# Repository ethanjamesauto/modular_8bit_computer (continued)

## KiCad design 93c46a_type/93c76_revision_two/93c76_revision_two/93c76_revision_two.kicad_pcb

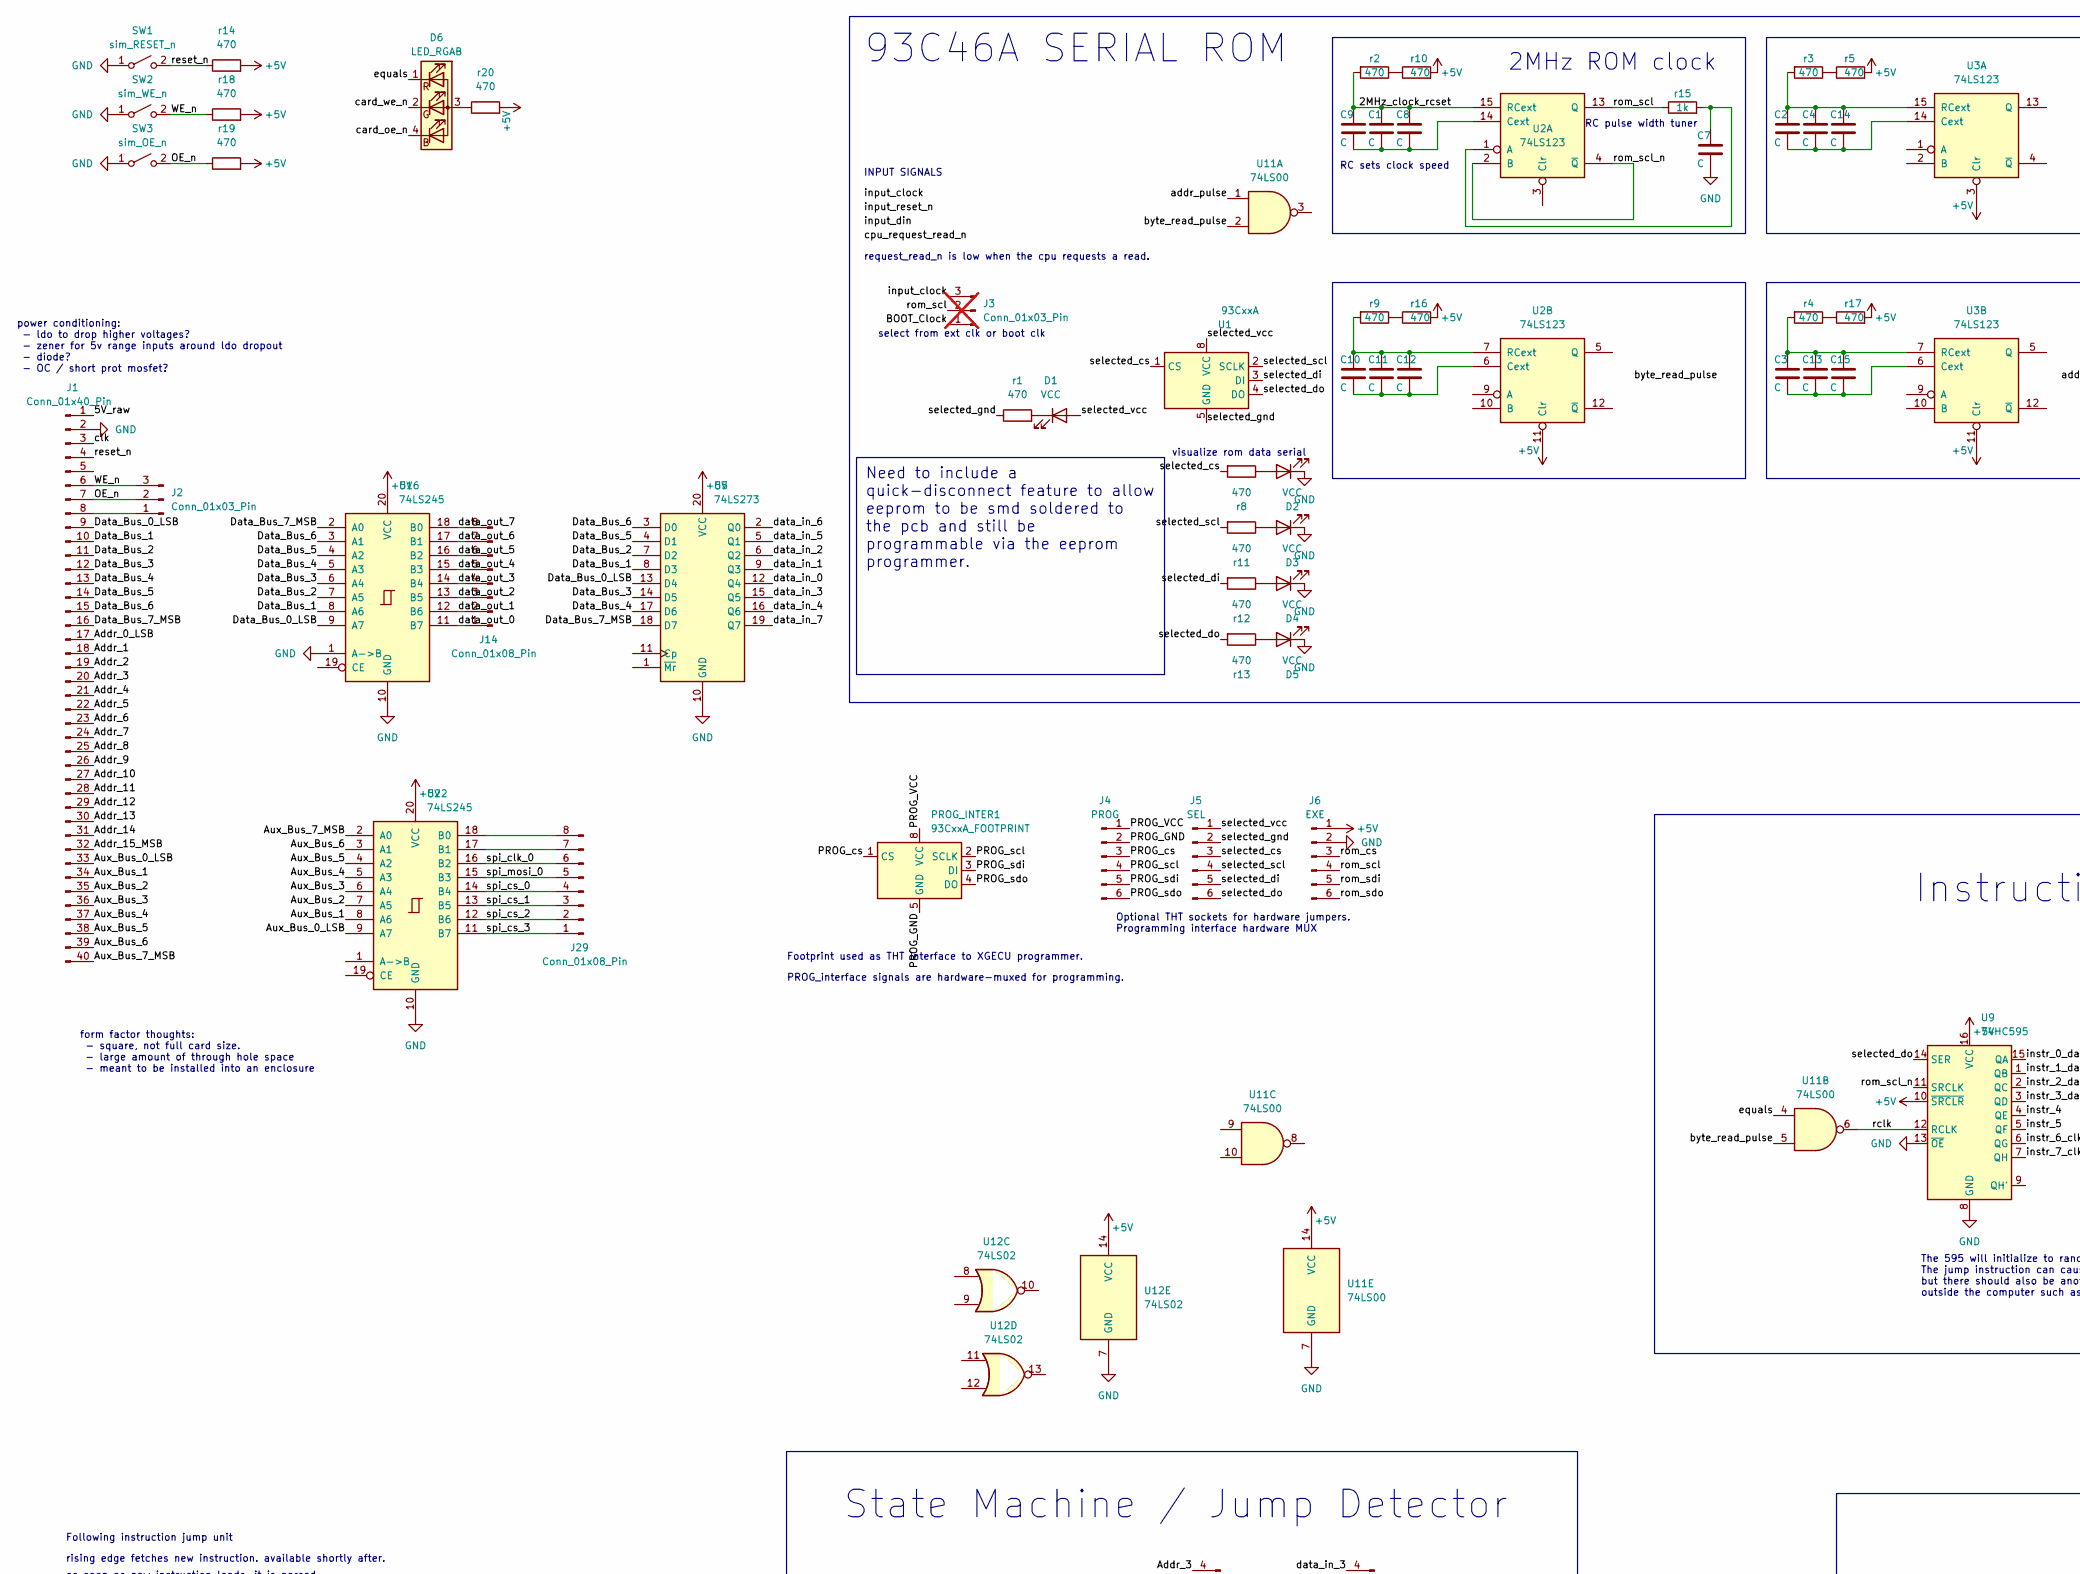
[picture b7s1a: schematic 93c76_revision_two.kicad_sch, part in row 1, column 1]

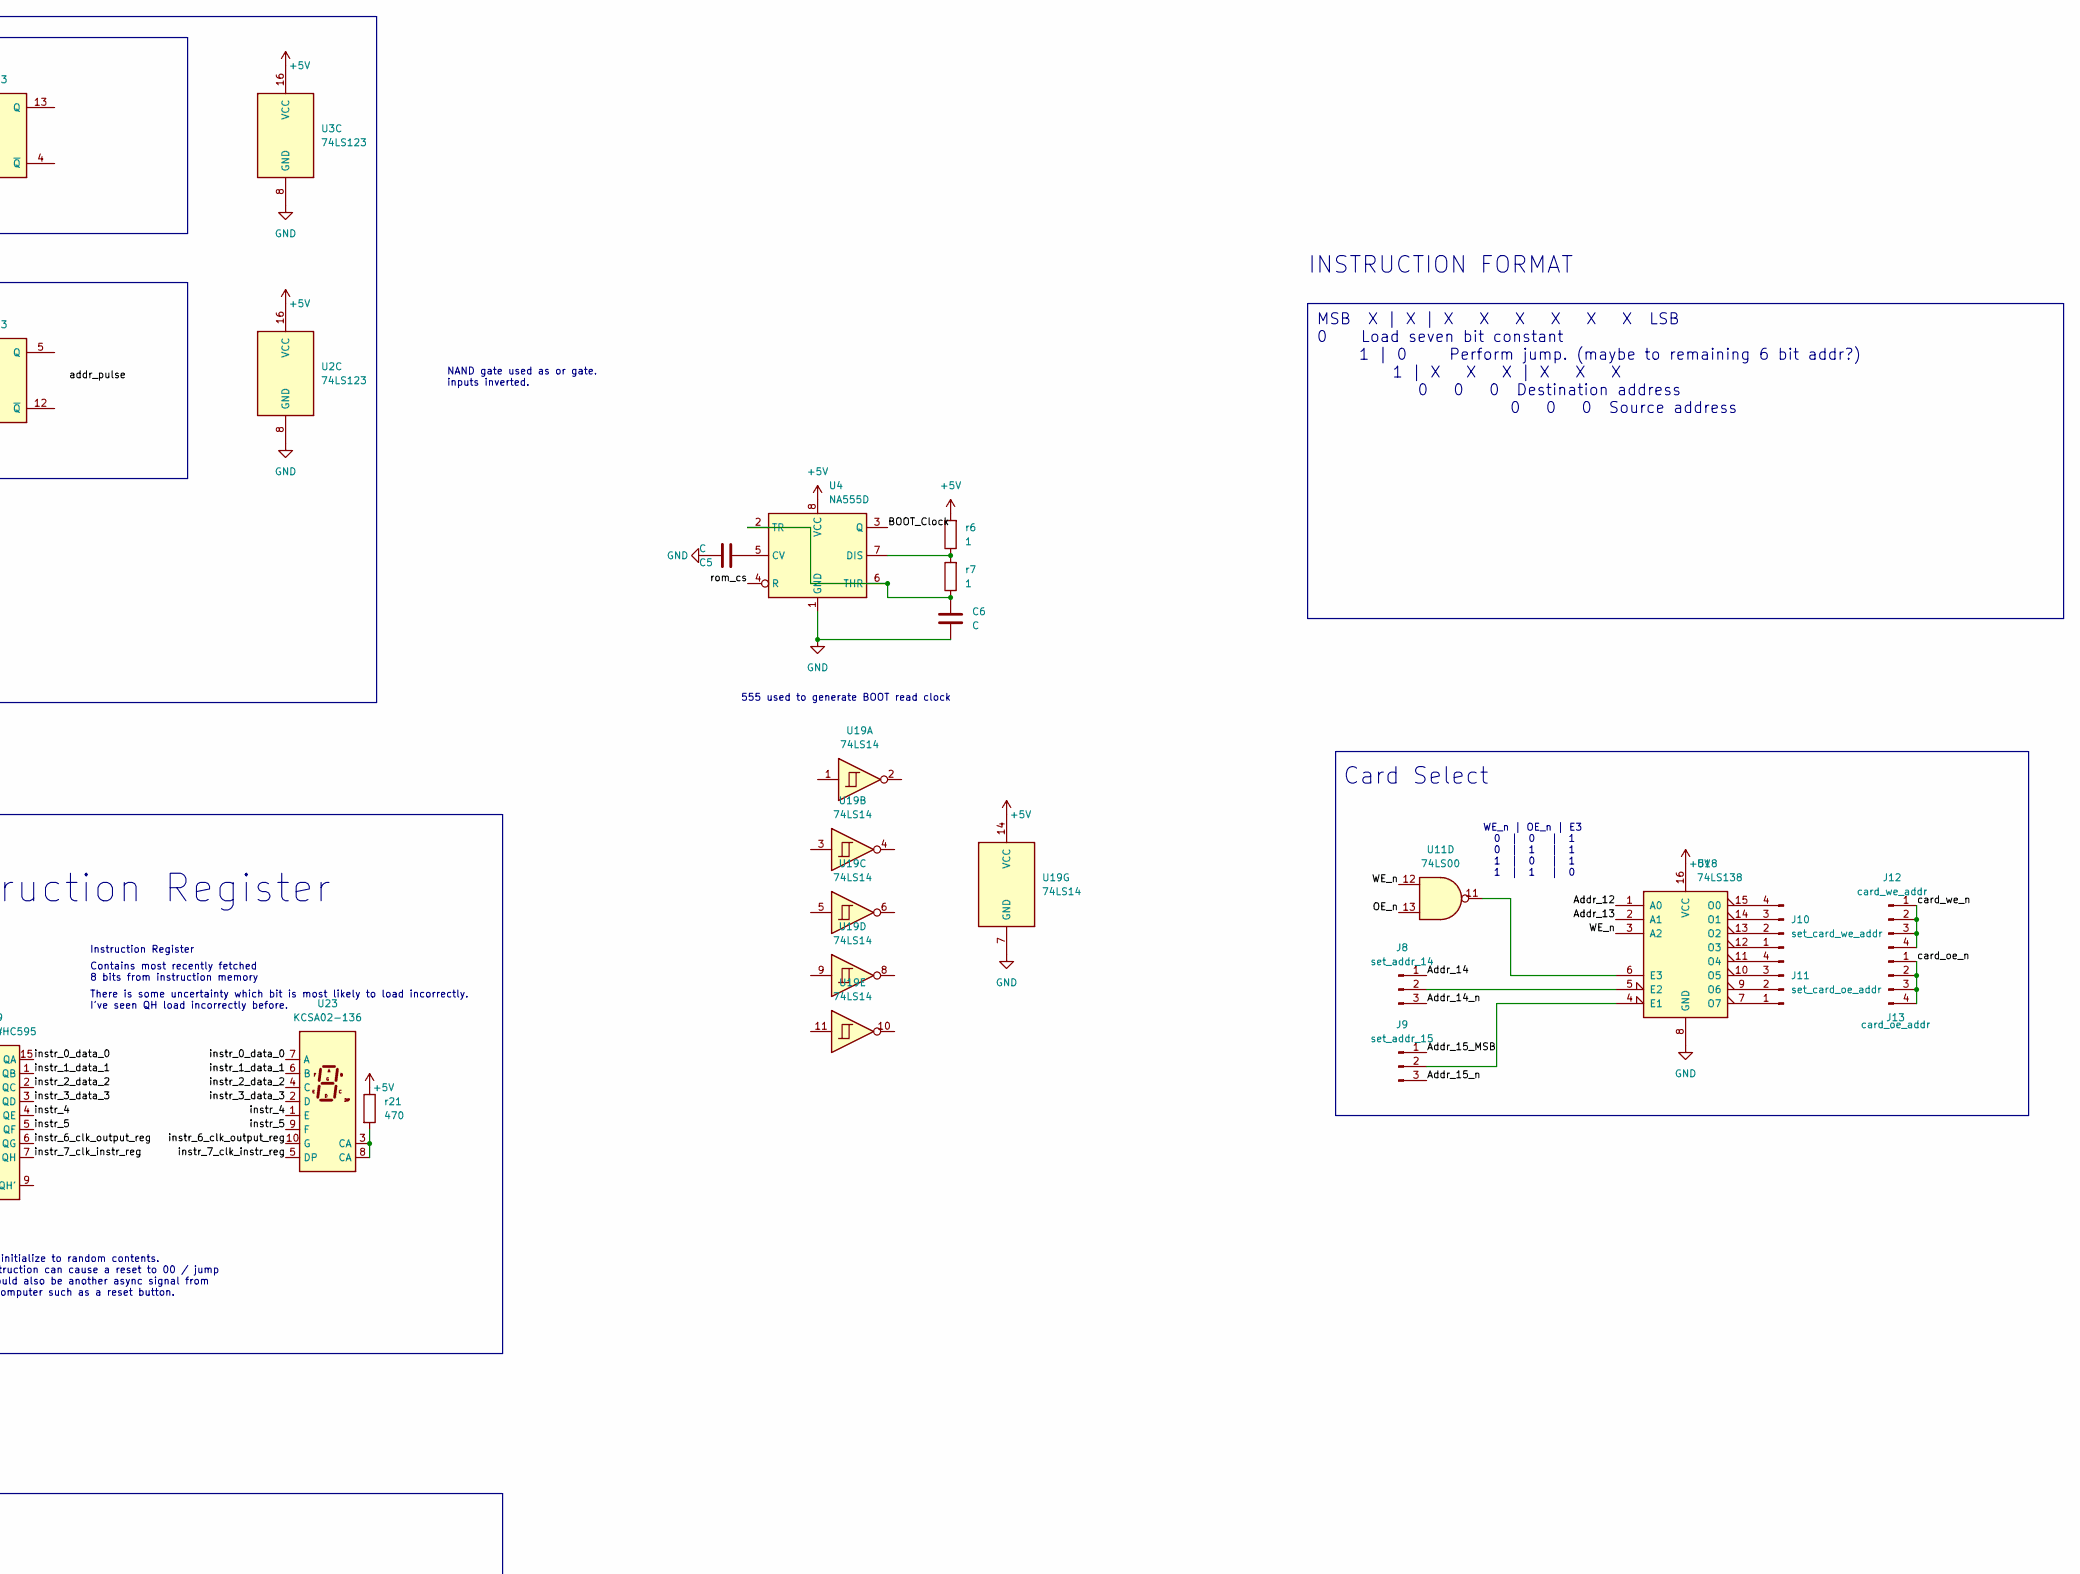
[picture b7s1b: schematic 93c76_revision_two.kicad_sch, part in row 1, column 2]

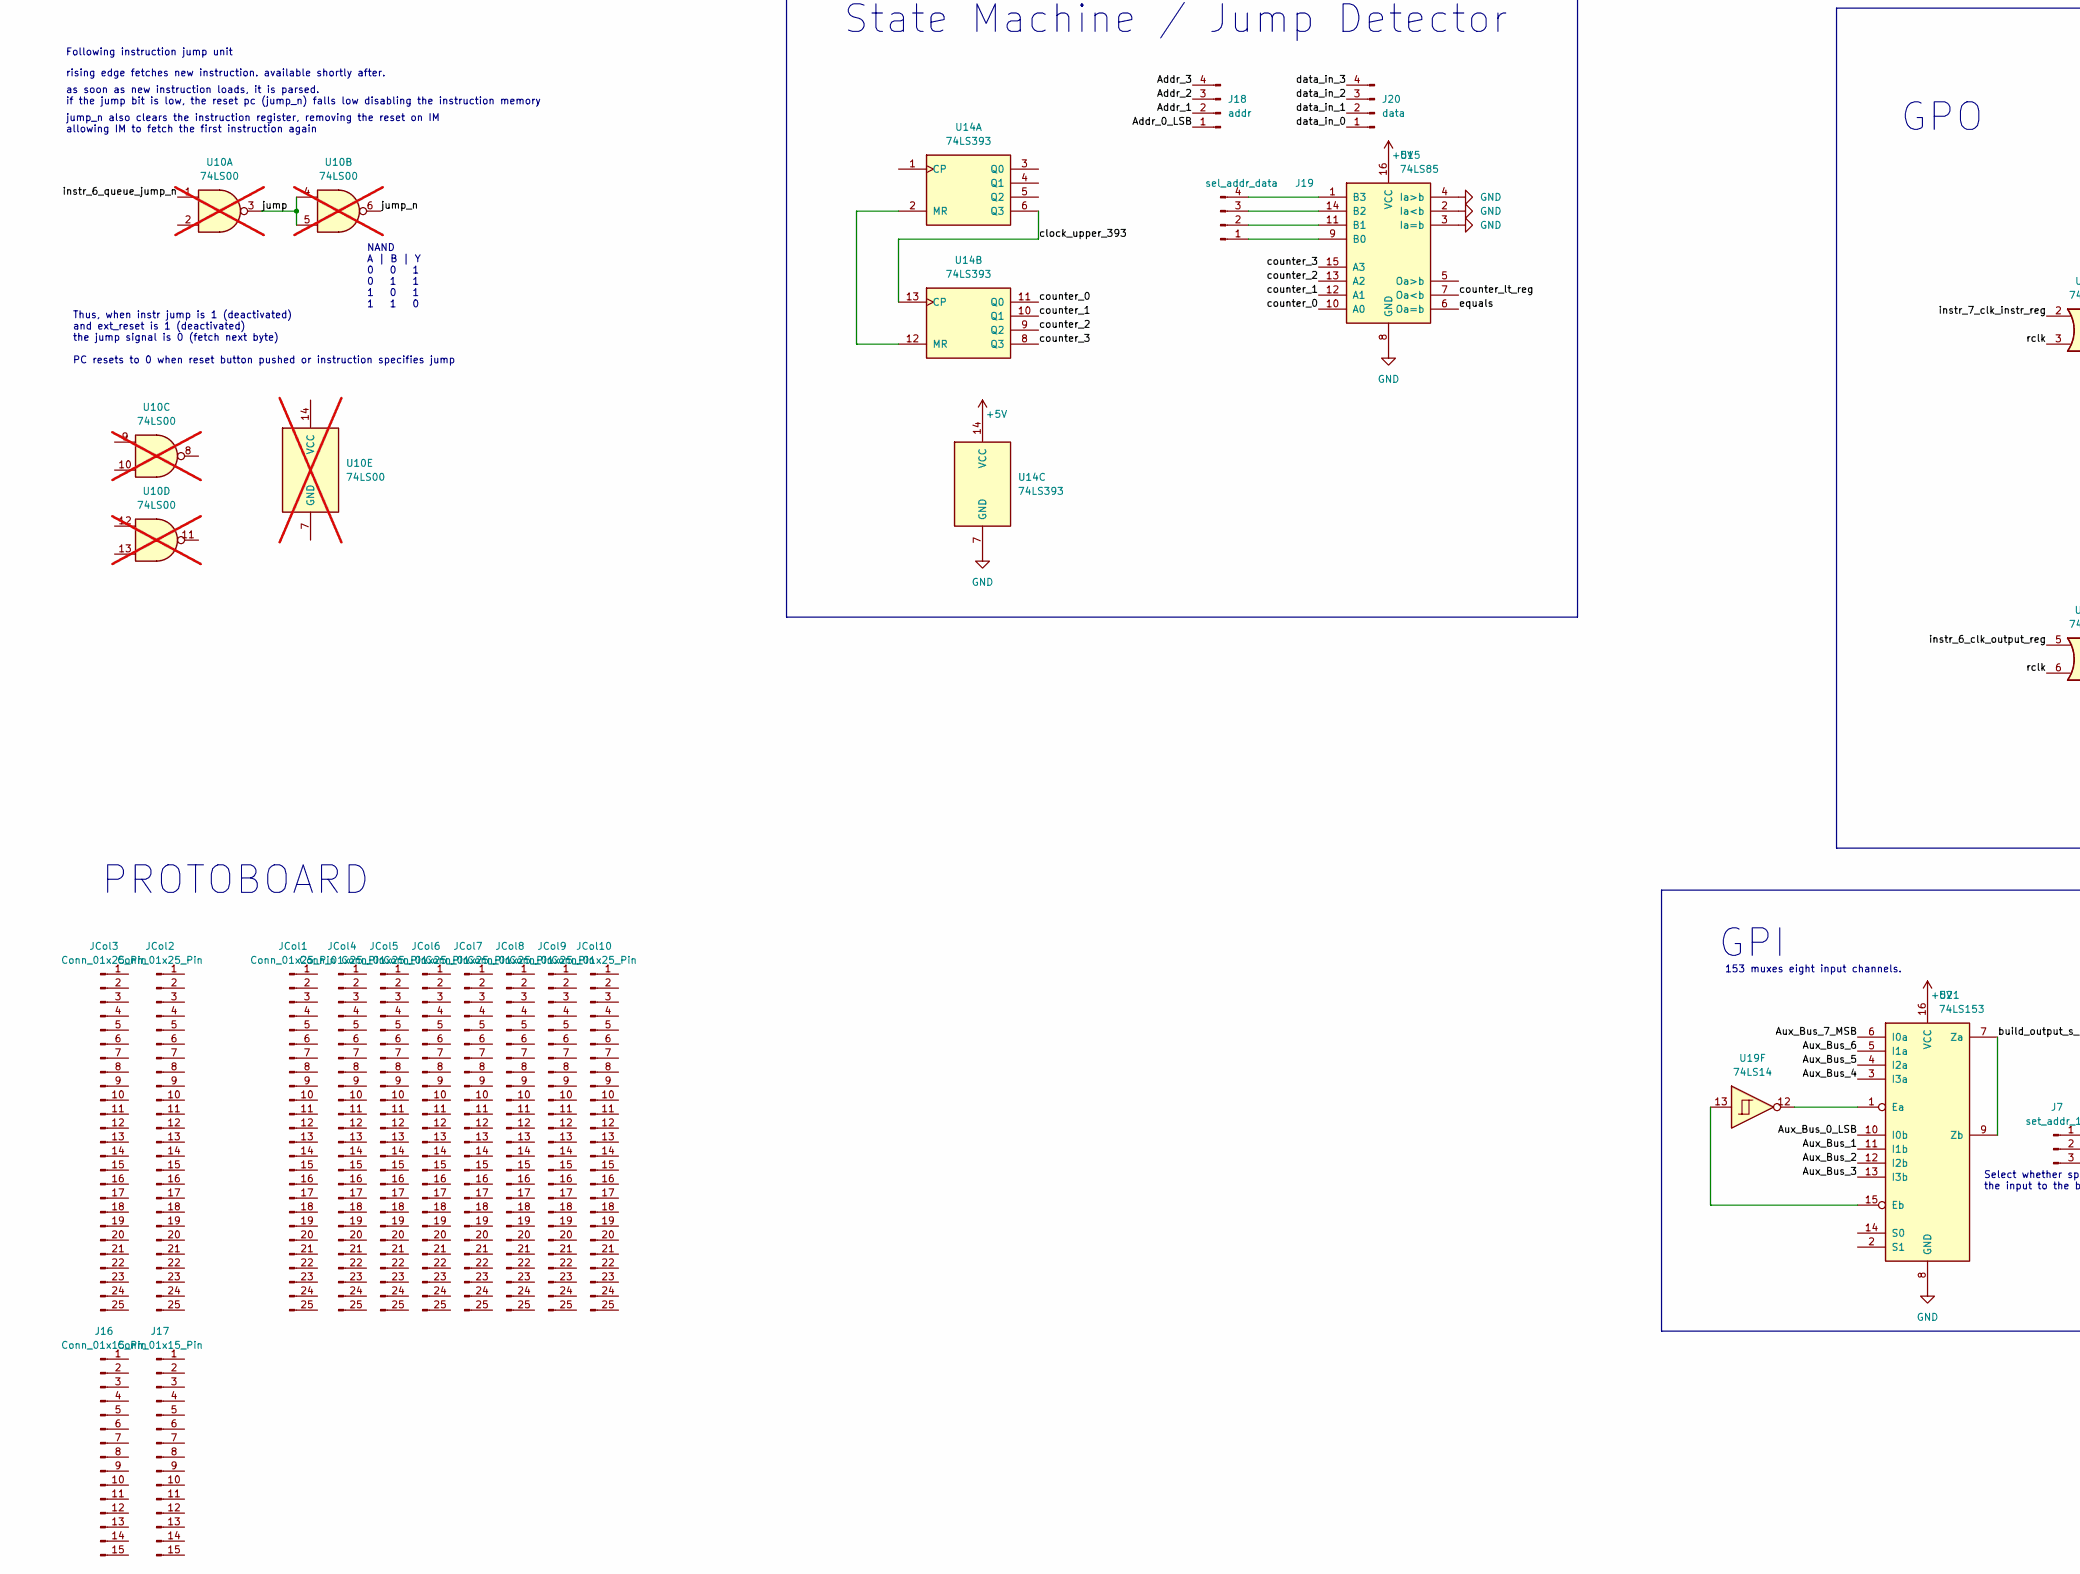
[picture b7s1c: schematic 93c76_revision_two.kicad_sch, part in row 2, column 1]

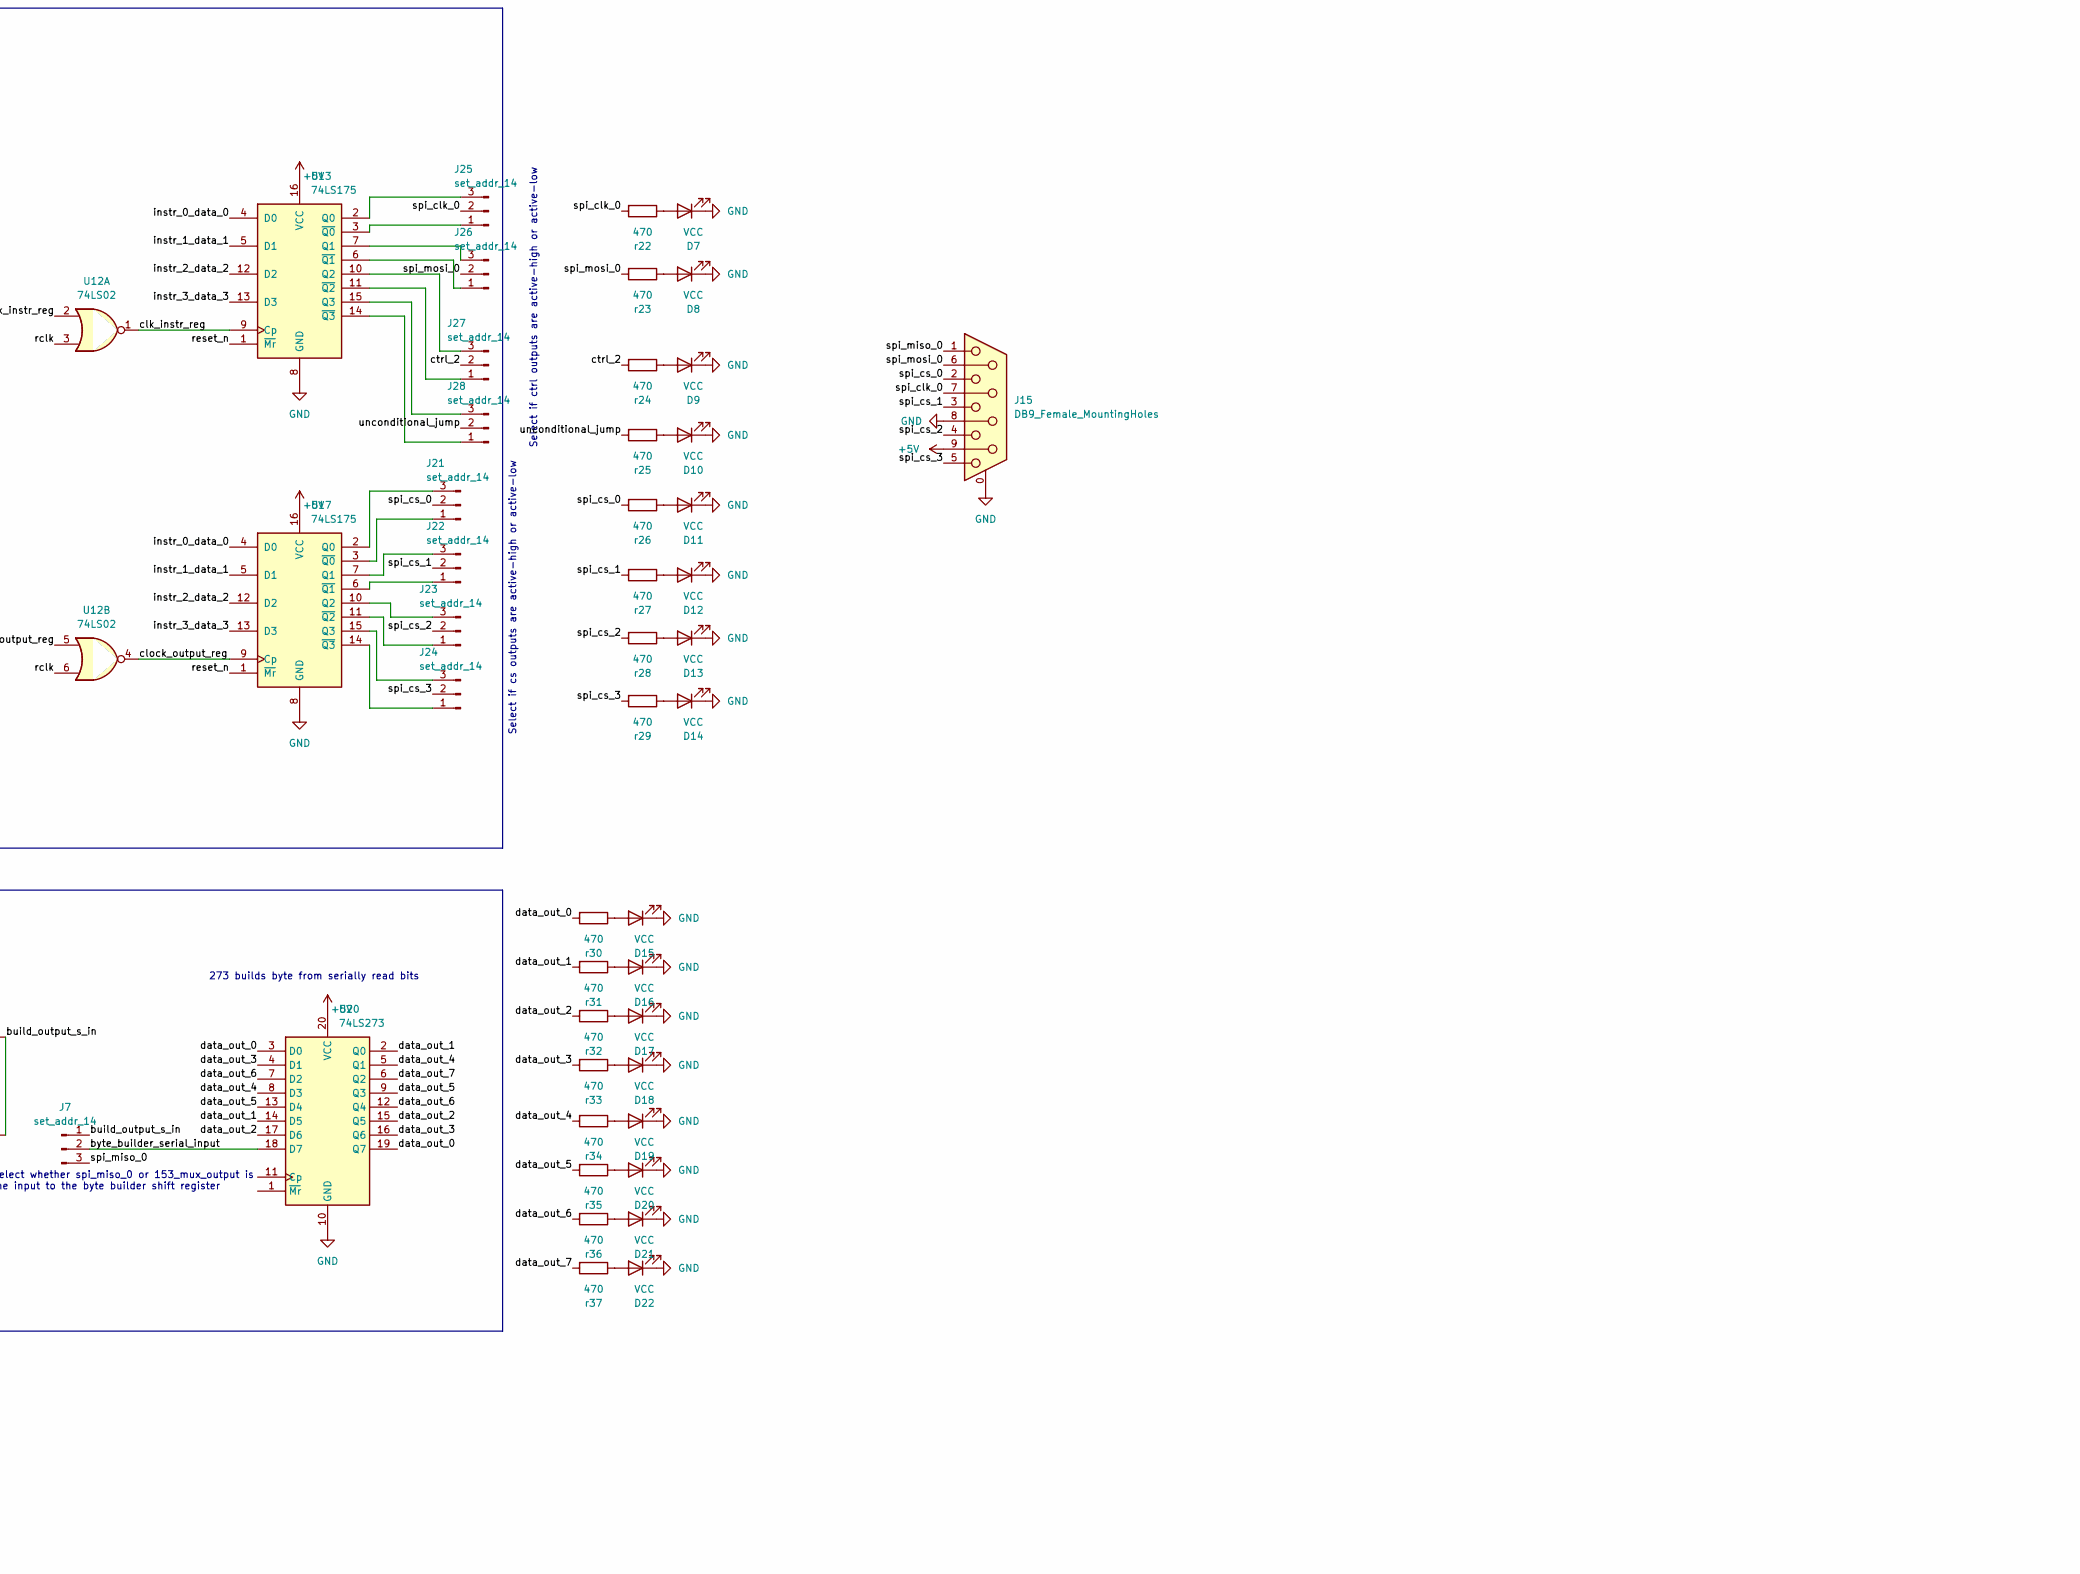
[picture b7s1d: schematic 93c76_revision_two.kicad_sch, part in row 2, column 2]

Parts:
C1, C2, C3, C4, C5, C6, C7, C8, C9, C10, C11, C12, C13, C14, C15: C; C_Disc_D3.0mm_W2.0mm_P2.50mm
D1, D2, D3, D4, D5, D7, D8, D9, D10, D11, D12, D13, D14, D15, D16, D17, D18, D19, D20, D21, D22: VCC; LED_0603_1608Metric_Pad1.05x0.95mm_HandSolder
D6: LED_RGAB; LED_D5.0mm-4_RGB
J1: Conn_01x40_Pin; PinHeader_1x40_P2.54mm_Horizontal
J2: Conn_01x03_Pin; PinHeader_1x03_P2.54mm_Vertical
J3: Conn_01x03_Pin; PinHeader_1x03_P2.54mm_Vertical; not fitted
J4: PROG; PinHeader_1x06_P2.54mm_Vertical
J5: SEL; PinHeader_1x06_P2.54mm_Vertical
J6: EXE; PinHeader_1x06_P2.54mm_Vertical
J7, J8, J21, J22, J23, J24, J25, J26, J27, J28: set_addr_14; PinHeader_1x03_P2.54mm_Vertical
J9: set_addr_15; PinHeader_1x03_P2.54mm_Vertical
J10: set_card_we_addr; PinHeader_1x04_P2.54mm_Vertical
J11: set_card_oe_addr; PinHeader_1x04_P2.54mm_Vertical
J12: card_we_addr; PinHeader_1x04_P2.54mm_Vertical
J13: card_oe_addr; PinHeader_1x04_P2.54mm_Vertical
J14, J29: Conn_01x08_Pin; PinHeader_1x08_P2.54mm_Vertical
J15: DB9_Female_MountingHoles; DSUB-9_Female_Horizontal_P2.77x2.84mm_EdgePinOffset4.94mm_H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
J16, J17: Conn_01x15_Pin; PinHeader_1x15_P2.54mm_Vertical
J18: addr; PinHeader_1x04_P2.54mm_Vertical
J19: sel_addr_data; PinHeader_1x04_P2.54mm_Vertical
J20: data; PinHeader_1x04_P2.54mm_Vertical
JCol1, JCol2, JCol3, JCol4, JCol5, JCol6, JCol7, JCol8, JCol9, JCol10: Conn_01x25_Pin; PinHeader_1x25_P2.54mm_Vertical
PROG_INTER1: 93CxxA_FOOTPRINT; DIP-8_W7.62mm
SW1: sim_RESET_n; R_Axial_DIN0204_L3.6mm_D1.6mm_P5.08mm_Horizontal
SW2: sim_WE_n; R_Axial_DIN0204_L3.6mm_D1.6mm_P5.08mm_Horizontal
SW3: sim_OE_n; R_Axial_DIN0204_L3.6mm_D1.6mm_P5.08mm_Horizontal
U1: 93CxxA; SOIC-8_3.9x4.9mm_P1.27mm
U2, U3: 74LS123; DIP-16_W7.62mm
U4: NA555D; DIP-8_W7.62mm
U5, U20: 74LS273; DIP-20_W7.62mm
U9: 74HC595; SOIC-16_3.9x9.9mm_P1.27mm
U10: 74LS00; not fitted
U11: 74LS00; DIP-14_W7.62mm
U12: 74LS02; DIP-14_W7.62mm
U13, U17: 74LS175; DIP-16_W7.62mm
U14: 74LS393; DIP-14_W7.62mm
U15: 74LS85; DIP-16_W7.62mm
U16, U22: 74LS245; DIP-20_W7.62mm
U18: 74LS138; DIP-16_W7.62mm
U19: 74LS14; DIP-14_W7.62mm
U21: 74LS153; DIP-16_W7.62mm
U23: KCSA02-136; 7SegmentLED_LTS6760_LTS6780
r1, r8, r11, r12, r13, r14, r18, r19, r20, r21, r22, r23, r24, r25, r26, r27, r28, r29, r30, r31, r32, r33, r34, r35, r36, r37: 470; R_0603_1608Metric_Pad0.98x0.95mm_HandSolder
r2, r3, r4, r5, r9, r10, r16, r17: 470; R_Axial_DIN0204_L3.6mm_D1.6mm_P7.62mm_Horizontal
r6, r7: 1; R_Axial_DIN0204_L3.6mm_D1.6mm_P7.62mm_Horizontal
r15: 1k; R_Axial_DIN0204_L3.6mm_D1.6mm_P7.62mm_Horizontal

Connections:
+5V: J6.1, J15.9, U2.11 (Clr), U2.16 (VCC), U3.3 (Clr), U3.11 (Clr), U3.16 (VCC), U4.8 (VCC), U5.20 (VCC), U9.10 (~SRCLR), U9.16 (VCC), U11.14 (VCC), U12.14 (VCC), U13.16 (VCC), U14.14 (VCC), U15.16 (VCC), U16.20 (VCC), U17.16 (VCC), U18.16 (VCC), U19.14 (VCC), U20.20 (VCC), U21.16 (VCC), U22.20 (VCC), r5.2, r6.2, r10.2, r14.2, r16.2, r17.2, r18.2, r19.2, r20.2, r21.1
/2MHz_clock_rcset: C1.2, C8.2, C9.2, U2.15 (RCext), r2.2
/5V_raw: J1.1
/Addr_0_LSB: J1.17, J18.1
/Addr_1: J1.18, J18.2
/Addr_2: J1.19, J18.3
/Addr_3: J1.20, J18.4
/Addr_4: J1.21
/Addr_5: J1.22
/Addr_6: J1.23
/Addr_7: J1.24
/Addr_8: J1.25
/Addr_9: J1.26
/Addr_10: J1.27
/Addr_11: J1.28
/Addr_12: J1.29, U18.1 (A0)
/Addr_13: J1.30, U18.2 (A1)
/Addr_14: J1.31, J8.1
/Addr_14_n: J8.3
/Addr_15_MSB: J1.32, J9.1
/Addr_15_n: J9.3
/Aux_Bus_0_LSB: J1.33, U21.10 (I0b), U22.9 (A7)
/Aux_Bus_1: J1.34, U21.11 (I1b), U22.8 (A6)
/Aux_Bus_2: J1.35, U21.12 (I2b), U22.7 (A5)
/Aux_Bus_3: J1.36, U21.13 (I3b), U22.6 (A4)
/Aux_Bus_4: J1.37, U21.3 (I3a), U22.5 (A3)
/Aux_Bus_5: J1.38, U21.4 (I2a), U22.4 (A2)
/Aux_Bus_6: J1.39, U21.5 (I1a), U22.3 (A1)
/Aux_Bus_7_MSB: J1.40, U21.6 (I0a), U22.2 (A0)
/BOOT_Clock: J3.1, U4.3 (Q)
/Data_Bus_0_LSB: J1.9, U5.13 (D4), U16.9 (A7)
/Data_Bus_1: J1.10, U5.8 (D3), U16.8 (A6)
/Data_Bus_2: J1.11, U5.7 (D2), U16.7 (A5)
/Data_Bus_3: J1.12, U5.14 (D5), U16.6 (A4)
/Data_Bus_4: J1.13, U5.17 (D6), U16.5 (A3)
/Data_Bus_5: J1.14, U5.4 (D1), U16.4 (A2)
/Data_Bus_6: J1.15, U5.3 (D0), U16.3 (A1)
/Data_Bus_7_MSB: J1.16, U5.18 (D7), U16.2 (A0)
/OE_n: J1.7, J2.2, SW3.2 (B), U11.13, r19.1
/PROG_GND: J4.2, PROG_INTER1.5 (GND)
/PROG_VCC: J4.1, PROG_INTER1.8 (VCC)
/PROG_cs: J4.3, PROG_INTER1.1 (CS)
/PROG_scl: J4.4, PROG_INTER1.2 (SCLK)
/PROG_sdi: J4.5, PROG_INTER1.3 (DI)
/PROG_sdo: J4.6, PROG_INTER1.4 (DO)
/WE_n: J1.6, J2.3, SW2.2 (B), U11.12, U18.3 (A2), r18.1
/addr_pulse: U11.1
/build_output_s_in: J7.1, U21.7 (Za), U21.9 (Zb)
/byte_builder_serial_input: J7.2, U20.18 (D7)
/byte_read_pulse: U11.2, U11.5
/card_oe_n: D6.4 (BK), J13.1, J13.2, J13.3, J13.4
/card_we_n: D6.2 (GK), J12.1, J12.2, J12.3, J12.4
/clk: J1.3
/clk_instr_reg: U12.1, U13.9 (Cp)
/clock_output_reg: U12.4, U17.9 (Cp)
/clock_upper_393: U14.6 (Q3), U14.13 (CP)
/counter_0: U14.11 (Q0), U15.10 (A0)
/counter_1: U14.10 (Q1), U15.12 (A1)
/counter_2: U14.9 (Q2), U15.13 (A2)
/counter_3: U14.8 (Q3), U15.15 (A3)
/counter_lt_reg: U15.7 (Oa<b)
/ctrl_2: J27.2, r24.2
/data_in_0: J20.1, U5.12 (Q4)
/data_in_1: J20.2, U5.9 (Q3)
/data_in_2: J20.3, U5.6 (Q2)
/data_in_3: J20.4, U5.15 (Q5)
/data_in_4: U5.16 (Q6)
/data_in_5: U5.5 (Q1)
/data_in_6: U5.2 (Q0)
/data_in_7: U5.19 (Q7)
/data_out_0: J14.1, U16.11 (B7), U20.3 (D0), U20.19 (Q7), r30.2
/data_out_1: J14.2, U16.12 (B6), U20.2 (Q0), U20.14 (D5), r31.2
/data_out_2: J14.3, U16.13 (B5), U20.15 (Q5), U20.17 (D6), r32.2
/data_out_3: J14.4, U16.14 (B4), U20.4 (D1), U20.16 (Q6), r33.2
/data_out_4: J14.5, U16.15 (B3), U20.5 (Q1), U20.8 (D3), r34.2
/data_out_5: J14.6, U16.16 (B2), U20.9 (Q3), U20.13 (D4), r35.2
/data_out_6: J14.7, U16.17 (B1), U20.7 (D2), U20.12 (Q4), r36.2
/data_out_7: J14.8, U16.18 (B0), U20.6 (Q2), r37.2
/equals: D6.1 (RK), U11.4, U15.6 (Oa=b)
/instr_0_data_0: U9.15 (QA), U13.4 (D0), U17.4 (D0), U23.7 (A)
/instr_1_data_1: U9.1 (QB), U13.5 (D1), U17.5 (D1), U23.6 (B)
/instr_2_data_2: U9.2 (QC), U13.12 (D2), U17.12 (D2), U23.4 (C)
/instr_3_data_3: U9.3 (QD), U13.13 (D3), U17.13 (D3), U23.2 (D)
/instr_4: U9.4 (QE), U23.1 (E)
/instr_5: U9.5 (QF), U23.9 (F)
/instr_6_clk_output_reg: U9.6 (QG), U12.5, U23.10 (G)
/instr_7_clk_instr_reg: U9.7 (QH), U12.2, U23.5 (DP)
/rclk: U9.12 (RCLK), U11.6, U12.3, U12.6
/reset_n: J1.4, SW1.2 (B), U13.1 (~Mr), U17.1 (~Mr), r14.1
/rom_cs: J6.3, U4.4 (R)
/rom_scl: J6.4, U2.13 (Q), r15.1
/rom_scl_n: U2.2 (B), U2.4 (~Q), U9.11 (SRCLK)
/rom_sdi: J6.5
/rom_sdo: J6.6
/selected_cs: J5.3, U1.1 (CS), r8.2
/selected_di: J5.5, U1.3 (DI), r12.2
/selected_do: J5.6, U1.4 (DO), U9.14 (SER), r13.2
/selected_gnd: J5.2, U1.5 (GND), r1.1
/selected_scl: J5.4, U1.2 (SCLK), r11.2
/selected_vcc: D1.2 (A), J5.1, U1.8 (VCC)
/spi_clk_0: J15.7, J25.2, J29.6, U22.16 (B2), r22.2
/spi_cs_0: J15.2, J21.2, J29.4, U22.14 (B4), r26.2
/spi_cs_1: J15.3, J22.2, J29.3, U22.13 (B5), r27.2
/spi_cs_2: J15.4, J23.2, J29.2, U22.12 (B6), r28.2
/spi_cs_3: J15.5, J24.2, J29.1, U22.11 (B7), r29.2
/spi_miso_0: J7.3, J15.1
/spi_mosi_0: J15.6, J26.2, J29.5, U22.15 (B3), r23.2
/unconditional_jump: J28.2, r25.2
GND: C5.2, C6.2, C7.1, D2.1 (K), D3.1 (K), D4.1 (K), D5.1 (K), D7.1 (K), D8.1 (K), D9.1 (K), D10.1 (K), D11.1 (K), D12.1 (K), D13.1 (K), D14.1 (K), D15.1 (K), D16.1 (K), D17.1 (K), D18.1 (K), D19.1 (K), D20.1 (K), D21.1 (K), D22.1 (K), J1.2, J6.2, J15.0 (PAD), J15.8, SW1.1 (A), SW2.1 (A), SW3.1 (A), U2.8 (GND), U3.8 (GND), U4.1 (GND), U5.10 (GND), U9.8 (GND), U9.13 (~OE), U11.7 (GND), U12.7 (GND), U13.8 (GND), U14.7 (GND), U15.2 (Ia<b), U15.3 (Ia=b), U15.4 (Ia>b), U15.8 (GND), U16.1 (A->B), U16.10 (GND), U17.8 (GND), U18.8 (GND), U19.7 (GND), U20.10 (GND), U21.8 (GND), U22.10 (GND)
unnamed: D1.1 (K), r1.2
unnamed: D2.2 (A), r8.1
unnamed: D3.2 (A), r11.1
unnamed: D4.2 (A), r12.1
unnamed: D5.2 (A), r13.1
unnamed: D6.3 (A), r20.1
unnamed: D7.2 (A), r22.1
unnamed: D8.2 (A), r23.1
unnamed: D9.2 (A), r24.1
unnamed: D10.2 (A), r25.1
unnamed: D11.2 (A), r26.1
unnamed: D12.2 (A), r27.1
unnamed: D13.2 (A), r28.1
unnamed: D14.2 (A), r29.1
unnamed: D15.2 (A), r30.1
unnamed: D16.2 (A), r31.1
unnamed: D17.2 (A), r32.1
unnamed: D18.2 (A), r33.1
unnamed: D19.2 (A), r34.1
unnamed: D20.2 (A), r35.1
unnamed: D21.2 (A), r36.1
unnamed: D22.2 (A), r37.1
unnamed: J1.8, J2.1
unnamed: J8.2, U18.5 (E2)
unnamed: J9.2, U18.4 (E1)
unnamed: J10.1, U18.12 (O3)
unnamed: J10.2, U18.13 (O2)
unnamed: J10.3, U18.14 (O1)
unnamed: J10.4, U18.15 (O0)
unnamed: J11.1, U18.7 (O7)
unnamed: J11.2, U18.9 (O6)
unnamed: J11.3, U18.10 (O5)
unnamed: J11.4, U18.11 (O4)
unnamed: J19.1, U15.9 (B0)
unnamed: J19.2, U15.11 (B1)
unnamed: J19.3, U15.14 (B2)
unnamed: J19.4, U15.1 (B3)
unnamed: J21.1, U17.3 (~Q0)
unnamed: J21.3, U17.2 (Q0)
unnamed: J22.1, U17.6 (~Q1)
unnamed: J22.3, U17.7 (Q1)
unnamed: J23.1, U17.11 (~Q2)
unnamed: J23.3, U17.10 (Q2)
unnamed: J24.1, U17.14 (~Q3)
unnamed: J24.3, U17.15 (Q3)
unnamed: J25.1, U13.3 (~Q0)
unnamed: J25.3, U13.2 (Q0)
unnamed: J26.1, U13.6 (~Q1)
unnamed: J26.3, U13.7 (Q1)
unnamed: J27.1, U13.11 (~Q2)
unnamed: J27.3, U13.10 (Q2)
unnamed: J28.1, U13.14 (~Q3)
unnamed: J28.3, U13.15 (Q3)
unnamed: J29.7, U22.17 (B1)
unnamed: J29.8, U22.18 (B0)
unnamed: C7.2, U2.1 (A), r15.2
unnamed: C1.1, C8.1, C9.1, U2.14 (Cext)
unnamed: C10.1, C11.1, C12.1, U2.6 (Cext)
unnamed: C10.2, C11.2, C12.2, U2.7 (RCext), r9.2
unnamed: C2.1, C4.1, C14.1, U3.14 (Cext)
unnamed: C2.2, C4.2, C14.2, U3.15 (RCext), r3.2
unnamed: C3.1, C13.1, C15.1, U3.6 (Cext)
unnamed: C3.2, C13.2, C15.2, U3.7 (RCext), r4.2
unnamed: C5.1, U4.5 (CV)
unnamed: U4.7 (DIS), r6.1, r7.2
unnamed: C6.1, U4.2 (TR), U4.6 (THR), r7.1
unnamed: U10.3, U10.4, U10.5
unnamed: U14.2 (MR), U14.12 (MR)
unnamed: U11.11, U18.6 (E3)
unnamed: U19.12, U21.1 (Ea)
unnamed: U19.13, U21.15 (Eb)
unnamed: U23.3 (CA), U23.8 (CA), r21.2
unnamed: r3.1, r5.1
unnamed: r2.1, r10.1
unnamed: r9.1, r16.1
unnamed: r4.1, r17.1

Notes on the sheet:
Need to include a quick-disconnect feature to allow eeprom to be smd soldered to the pcb and still be programmable via the eeprom programmer.
MSB X | X | X X X X X X LSB 0 Load seven bit constant 1 | 0 Perform jump. (maybe to remaining 6 bit addr?) 1 | X X X | X X X 0 0 0 Destination address 0 0 0 Source address
93C46A SERIAL ROM
153 muxes eight input channels.
GPO
Thus, when instr jump is 1 (deactivated) and ext_reset is 1 (deactivated) the jump signal is 0 (fetch next byte) PC resets to 0 when reset button pushed or instruction specifies jump
INSTRUCTION FORMAT
Optional THT sockets for hardware jumpers. Programming interface hardware MUX
rising edge fetches new instruction. available shortly after.
Select if cs outputs are active-high or active-low
PROG_interface signals are hardware-muxed for programming.
Instruction Register
form factor thoughts: - square, not full card size. - large amount of through hole space - meant to be installed into an enclosure
as soon as new instruction loads, it is parsed. if the jump bit is low, the reset pc (jump_n) falls low disabling the instruction memory
The 595 will initialize to random contents. The jump instruction can cause a reset to 00 / jump but there should also be another async signal from outside the computer such as a reset button.
WE_n | OE_n | E3 0 | 0 | 1 0 | 1 | 1 1 | 0 | 1 1 | 1 | 0
jump_n also clears the instruction register, removing the reset on IM allowing IM to fetch the first instruction again
RC pulse width tuner
Select if ctrl outputs are active-high or active-low
State Machine / Jump Detector
power conditioning: - ldo to drop higher voltages? - zener for 5v range inputs around ldo dropout - diode? - OC / short prot mosfet?
INPUT SIGNALS
555 used to generate BOOT read clock
request_read_n is low when the cpu requests a read.
RC sets clock speed
Select whether spi_miso_0 or 153_mux_output is the input to the byte builder shift register
There is some uncertainty which bit is most likely to load incorrectly. I've seen QH load incorrectly before.
select from ext clk or boot clk
Contains most recently fetched 8 bits from instruction memory
NAND A | B | Y 0 0 1 0 1 1 1 0 1 1 1 0
Card Select
2MHz ROM clock
PROTOBOARD
visualize rom data serial
NAND gate used as or gate. inputs inverted.
Footprint used as THT interface to XGECU programmer.
GPI
273 builds byte from serially read bits
Following instruction jump unit

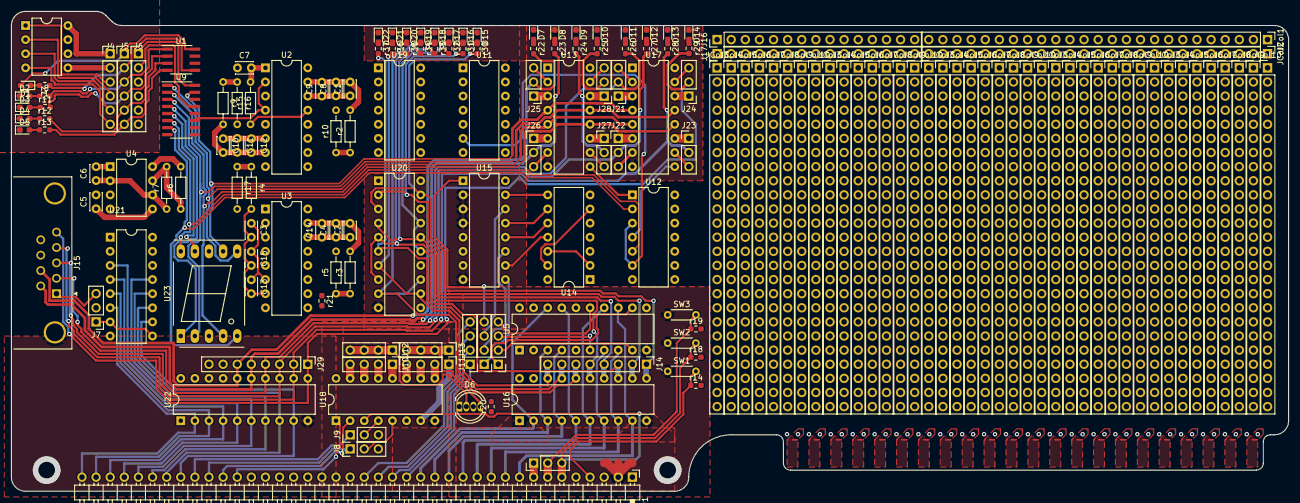
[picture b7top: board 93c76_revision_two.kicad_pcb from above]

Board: 2 copper layers, 229.9 x 86.4 mm, 167 parts (0 on the bottom side), 163 nets.

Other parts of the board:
JCol3#2, JCol3#3, JCol3#4, JCol3#5, JCol4#2, JCol4#3, JCol4#4, JCol4#5, JCol5#2, JCol5#3, JCol5#4, JCol5#5, JCol6#2, JCol6#3, JCol6#4, JCol6#5, JCol7#2, JCol7#3, JCol7#4, JCol7#5, JCol8#2, JCol8#3, JCol8#4, JCol8#5, JCol9#2, JCol9#3, JCol9#4, JCol9#5, JCol10#2, JCol10#3, JCol10#4, JCol10#5: Conn_01x25_Pin; PinHeader_1x25_P2.54mm_Vertical
